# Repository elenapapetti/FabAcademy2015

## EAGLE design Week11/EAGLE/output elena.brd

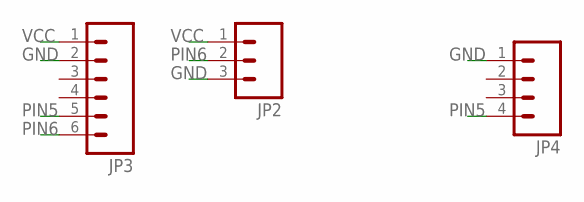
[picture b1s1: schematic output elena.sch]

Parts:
JP2: M031X03_NO_SILK; 1X03_NO_SILK
JP3: M06LONGPADS; 1X06_LONGPADS
JP4: M04LONGPADS; 1X04_LONGPADS

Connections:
GND: JP2.3, JP3.2, JP4.1
PIN5: JP3.5, JP4.4
PIN6: JP2.2, JP3.6
VCC: JP2.1, JP3.1

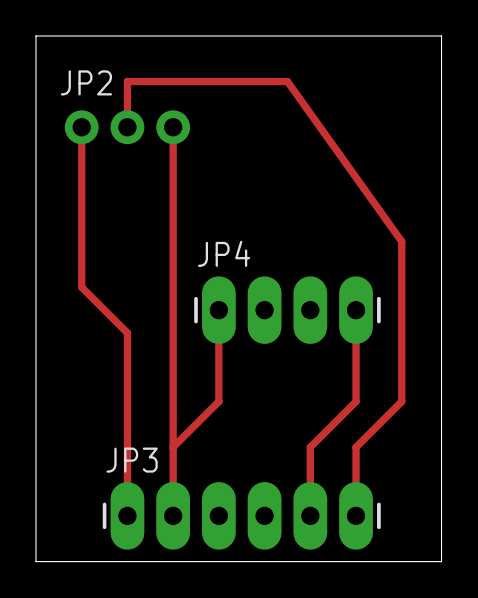
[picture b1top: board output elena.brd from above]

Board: 2 copper layers, 22.5 x 29.2 mm, 3 parts (0 on the bottom side), 4 nets.

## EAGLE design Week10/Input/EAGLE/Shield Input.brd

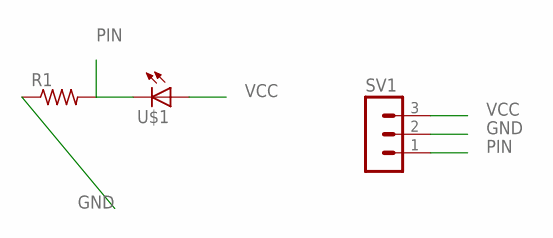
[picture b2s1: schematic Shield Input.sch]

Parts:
R1: RESISTOR1206; 1206
SV1: MA03-1
U$1: LED5MM; 5MM

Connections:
GND: R1.1, SV1.2
PIN: R1.2, SV1.1, U$1.OUT (C)
VCC: SV1.3, U$1.IN (A)

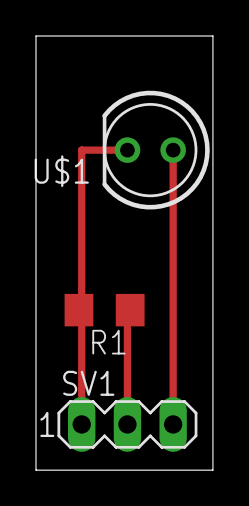
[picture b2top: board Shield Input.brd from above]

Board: 2 copper layers, 9.8 x 24.1 mm, 3 parts (0 on the bottom side), 3 nets.

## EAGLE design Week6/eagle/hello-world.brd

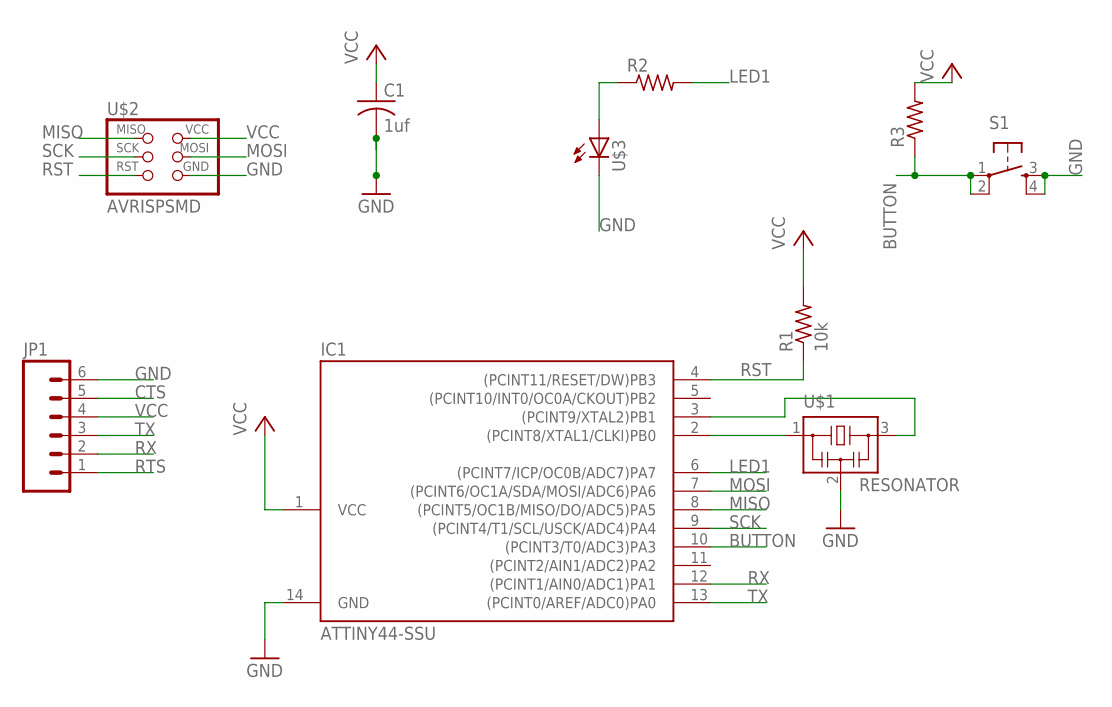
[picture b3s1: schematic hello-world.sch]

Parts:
C1: 1uf; C1206
IC1: ATTINY44-SSU; SOIC14
JP1: M06SMD; 1X06-SMD
R1: 10k; R1206
R2, R3: RESISTOR1206; 1206
S1: 6MM_SWITCH6MM_SWITCH; 6MM_SWITCH
U$1: RESONATOR; EFOBM
U$2: AVRISPSMD; 2X03SMD
U$3: LED1206; 1206

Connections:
BUTTON: IC1.10 ((PCINT3/T0/ADC3)PA3), R3.1, S1.1, S1.2 (P1)
CTS: JP1.5
GND: C1.2, IC1.14 (GND), JP1.6, S1.3 (S), S1.4 (S1), U$1.2, U$2.6 (GND), U$3.2 (C)
LED1: IC1.6 ((PCINT7/ICP/OC0B/ADC7)PA7), R2.2
MISO: IC1.8 ((PCINT5/OC1B/MISO/DO/ADC5)PA5), U$2.1 (MISO)
MOSI: IC1.7 ((PCINT6/OC1A/SDA/MOSI/ADC6)PA6), U$2.4 (MOSI)
unnamed: IC1.2 ((PCINT8/XTAL1/CLKI)PB0), U$1.1
unnamed: IC1.3 ((PCINT9/XTAL2)PB1), U$1.3
unnamed: R2.1, U$3.1 (A)
RST: IC1.4 ((PCINT11/RESET/DW)PB3), R1.1, U$2.5 (RST)
RTS: JP1.1
RX: IC1.12 ((PCINT1/AIN0/ADC1)PA1), JP1.2
SCK: IC1.9 ((PCINT4/T1/SCL/USCK/ADC4)PA4), U$2.3 (SCK)
TX: IC1.13 ((PCINT0/AREF/ADC0)PA0), JP1.3
VCC: C1.1, IC1.1 (VCC), JP1.4, R1.2, R3.2, U$2.2 (VCC)

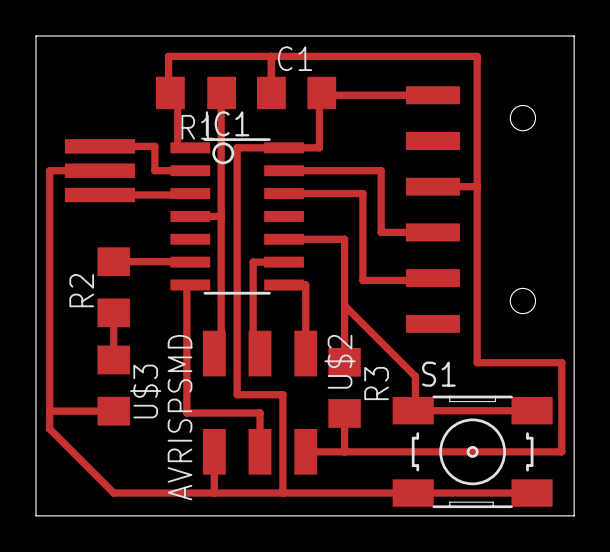
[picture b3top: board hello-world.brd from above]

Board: 1 copper layer, 29.9 x 26.7 mm, 10 parts (0 on the bottom side), 13 nets.

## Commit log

2015-03-30 Create Schedule
2015-03-30 Rename Schedule to Week1
2015-03-30 Create Week2
2015-03-30 Create Week3
2015-05-12 upload repository files
2015-06-19 upload files mechanical
2015-06-19 upload mechanical 2
2015-06-21 update week16
2015-06-25 update files
2015-06-26 Delete fabkit_v0.4.sch
    wrong files
2015-06-26 Delete fabkit_v0.4.brd
    wrong file
2015-06-28 aggiornamento files
2015-06-29 files final

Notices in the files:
parts and their libraries:
01_SparkFun: Licensing: CC v3.0 Share-Alike You are welcome to use this library for commercial purposes.
